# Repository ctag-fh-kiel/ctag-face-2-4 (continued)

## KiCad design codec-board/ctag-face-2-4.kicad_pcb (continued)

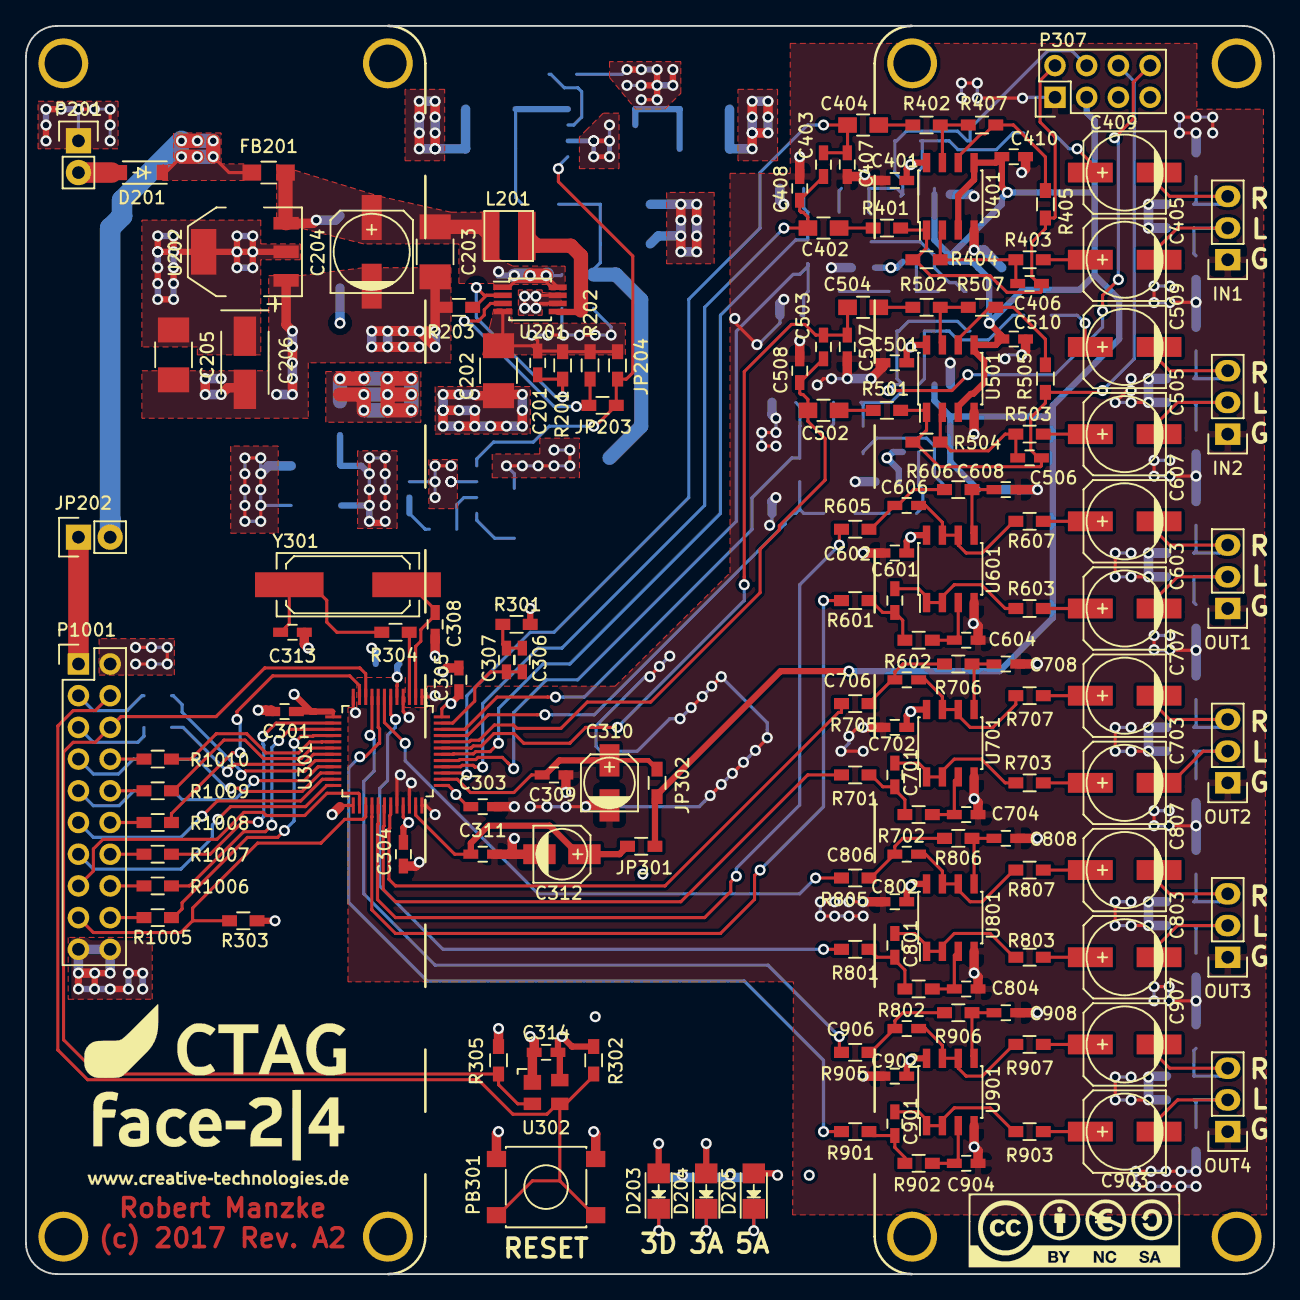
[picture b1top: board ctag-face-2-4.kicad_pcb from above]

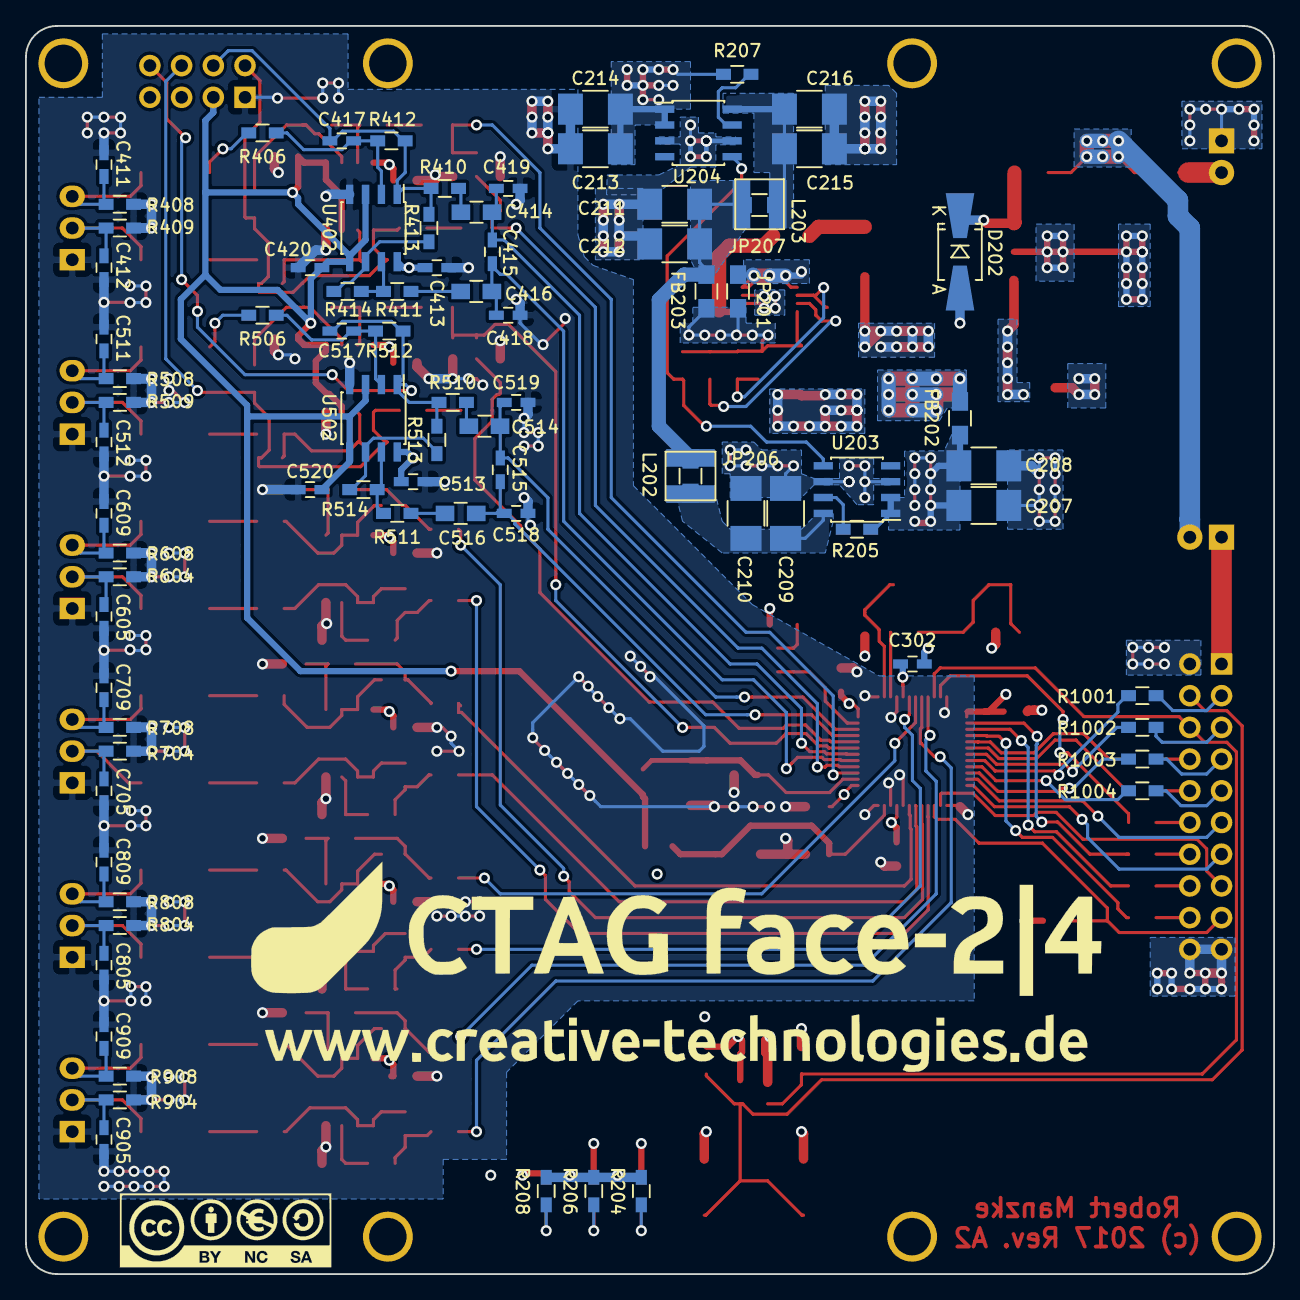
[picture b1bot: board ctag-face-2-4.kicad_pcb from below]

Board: 4 copper layers, 100.0 x 100.0 mm, 241 parts (84 on the bottom side), 143 nets.

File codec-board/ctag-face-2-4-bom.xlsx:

Mouser | Id | Designator | Package | Quantity | Designation | MfrNum | Remarks
x | 1 | C509,C204,C405,C409,C505,C603,C607,C703,C707,C803,C807,C903,C907 | c_elec_6.3x5.7 | 13 | 47uF | EEE-FC1C470P | Panasonic FC Type
x | 2 | C201 | C_0603_HandSoldering | 1 | 33pF | VJ0603A330JXACW1BC
x | 3 | C202 | C_1210_HandSoldering | 1 | 22uF | C3225X7R1C226K250AC | 10% X7R Highest Voltage Type possible
x | 4 | C203,C205,C207,C208,C209,C210,C211,C212,C213,C214,C215,C216 | C_1210_HandSoldering | 12 | 10uF | GRM32DR71E106KA12L | 10% X7R Highest Voltage Type possible
x | 5 | C206 | TantalC_SizeA_EIA-3216_HandSoldering | 1 | 100uF | TCNK107M006R0200
x | 6 | C301,C302,C303,C304,C305,C309,C311,C314,C401,C410,C413,C420,C501,C510,C513,C520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 | C_0603_HandSoldering | 20 | 100nF | C0603C104K5RACTU
x | 7 | C306 | C_0603_HandSoldering | 1 | 390pF | GRM1885C1H391JA01D
x | 8 | C307 | C_0603_HandSoldering | 1 | 5,6nF | C0603C562J5GACTU
x | 9 | C308,C313 | C_0603_HandSoldering | 2 | 22pF | C0603C220J5GACTU
x | 10 | C310,C312 | c_elec_4x5.7 | 2 | 10uF | EEE-FC1C100R
x | 11 | C402,C404,C414,C416,C502,C504,C514,C516 | C_0805_HandSoldering | 8 | 10uF | GRM21BR71A106KA73L
x | 12 | C403,C411,C412,C415,C503,C511,C512,C515 | C_0603_HandSoldering | 8 | 100pF | C0603C101J5GACTU
x | 13 | C406,C417,C506,C517,C601,C606,C701,C706,C801,C806,C901,C906 | C_0603_HandSoldering | 12 | 270pF | GRM1885C1H271JA01D
x | 14 | C407,C408,C418,C419,C507,C508,C518,C519 | C_0603_HandSoldering | 8 | 1nF | GCM188R71H102KA37D
x | 15 | C604,C608,C704,C708,C804,C808,C904,C908 | C_0603_HandSoldering | 8 | 200pF | GRM1885C2A201JA01D
x | 16 | C605,C609,C705,C709,C805,C809,C905,C909 | C_0603_HandSoldering | 8 | 3,3nF | C0603C332K5RACTU
x | 17 | D201 | SOD-123 | 1 | D_Schottky | STPS140Z
x | 18 | D203 | LED-1206 | 1 | LED3V3D | SML-LX1206GC-TR1
x | 19 | D204 | LED-1206 | 1 | LED3V3A | SML-LX1206GC-TR1
x | 20 | D205 | LED-1206 | 1 | LED5VA | SML-LX1206GC-TR1
x | 21 | JP201,JP206,JP207 | R_0805_HandSoldering | 3 | Jumper_NO_Small | RC0805JR-070RL
x | 22 | JP203,JP204,JP301,JP302 | R_0603_HandSoldering | 4 | Jumper_NO_Small | ERJ-3GEY0R00V
x | 23 | R201 | R_0603_HandSoldering | 1 | 115k | ERJ-3EKF1153V | Resistors all probably 1%, except digital section
x | 24 | R202,R303 | R_0603_HandSoldering | 2 | 1M | ERJ-3EKF1004V
x | 25 | R203 | R_0603_HandSoldering | 1 | 32k4 | ERJ-3EKF3242V
x | 26 | R204,R206 | R_0603_HandSoldering | 2 | 270 | ERJ-3EKF2700V
x | 27 | R205,R207,R302,R305,R408,R409,R508,R509,R604,R608,R704,R708,R804,R808,R904,R908 | R_0603_HandSoldering | 16 | 100k | ERJ-3EKF1003V
x | 28 | R208 | R_0603_HandSoldering | 1 | 620 | ERJ-3EKF6200V
x | 29 | R301 | R_0603_HandSoldering | 1 | 562 | ERJ-3EKF5620V
x | 30 | R304 | R_0603_HandSoldering | 1 | 100 | ERJ-3EKF1000V
x | 31 | R401,R402,R410,R411,R501,R502,R510,R511 | R_0603_HandSoldering | 8 | 237 | ERJ-3EKF2370V
x | 32 | R403,R404,R405,R406,R407,R412,R413,R414,R503,R504,R505,R506,R507,R512,R513,R514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 | R_0603_HandSoldering | 32 | 5k36 | ERJ-3EKF5361V
x | 33 | R603,R607,R703,R707,R803,R807,R903,R907 | R_0603_HandSoldering | 8 | 301 | ERJ-3EKF3010V
x | 34 | R1001,R1002,R1003,R1004,R1005,R1006,R1007,R1008,R1009,R1010 | R_0603_HandSoldering | 10 | 51 | ERJ-3EKF51R0V
x | 35 | SW301 | SW_SPST_PTS645 | 1 | SW_PUSH | PTS645SM43SMTR 92 LFS
x | 36 | U201 | MSOP-8_3x3mm_Pitch0.65mm | 1 | MCP1642B-ADJI/MS | MCP1642B-ADJI/MS
x | 37 | U202 | SOT-223 | 1 | TLV1117 | TLV1117-33IDCYR
x | 38 | U203 | SOIC-8_3.9x4.9mm_Pitch1.27mm | 1 | ADP7102ARDZ-3.3-R7 | ADP7102ARDZ-3.3-R7
x | 39 | U203,U204 | SOIC-8_3.9x4.9mm_Pitch1.27mm | 1 | ADP7102ARDZ-5.0-R7 | ADP7102ARDZ-5.0-R7
x | 40 | U301 | LQFP-48_7x7mm_Pitch0.5mm | 1 | AD1938 | AD1938YSTZ
x | 41 | U302 | SOT-143 | 1 | ADM811TARTZ | ADM811TARTZ-REEL7
x | 42 | U401,U402,U501,U502,U601,U701,U801,U901 | SOIC-8_3.9x4.9mm_Pitch1.27mm | 8 | 2CH-OPAMP | LME49721MAX/NOPB
x | 43 | Y301 | Q_49U3HMS | 1 | 24,576MHz | AT-24.576MAGK-T | Alternative
x | 44 | Y301 | Q_49U3HMS | 1 | 12,288MHz | AT-12.288MAGE-T
x | 45 | D202 | Diode-Universal-SMA-SMB_Handsoldering | 1 | FM4002 | FM4002
x | 46 | FB201,FB203 | R_0805_HandSoldering | 2 | 330R | 742792037 | Würth Beads
x | 47 | FB202 | R_0805_HandSoldering | 1 | 600R | 742792040
x | 48 | L201,L202,L203 | LPS4018 | 3 | 4.7uH | LPS4018-472MRC
x | 49 | P307 | DIL Socket 4+4 | 1 | ~ | M20-7830446 | Reichelt
x | 50 |  | Stiftleiste 40 Pins RM2,54 | 1 |  | M20-9734045
x | 51 |  | DIL Socket 10+10 | 1 |  | M20-7831046
x | 52 | C207, C208, C213, C214 | Alternative Configuration | 4 | 1uF | GRM32RR71H105KA01L | Configuration according to data sheet of ADPxxx
x | 53 | R604, R608 etc. | Alternative Configuration | 8 | 49k9 | ERJ-3EKF4992V

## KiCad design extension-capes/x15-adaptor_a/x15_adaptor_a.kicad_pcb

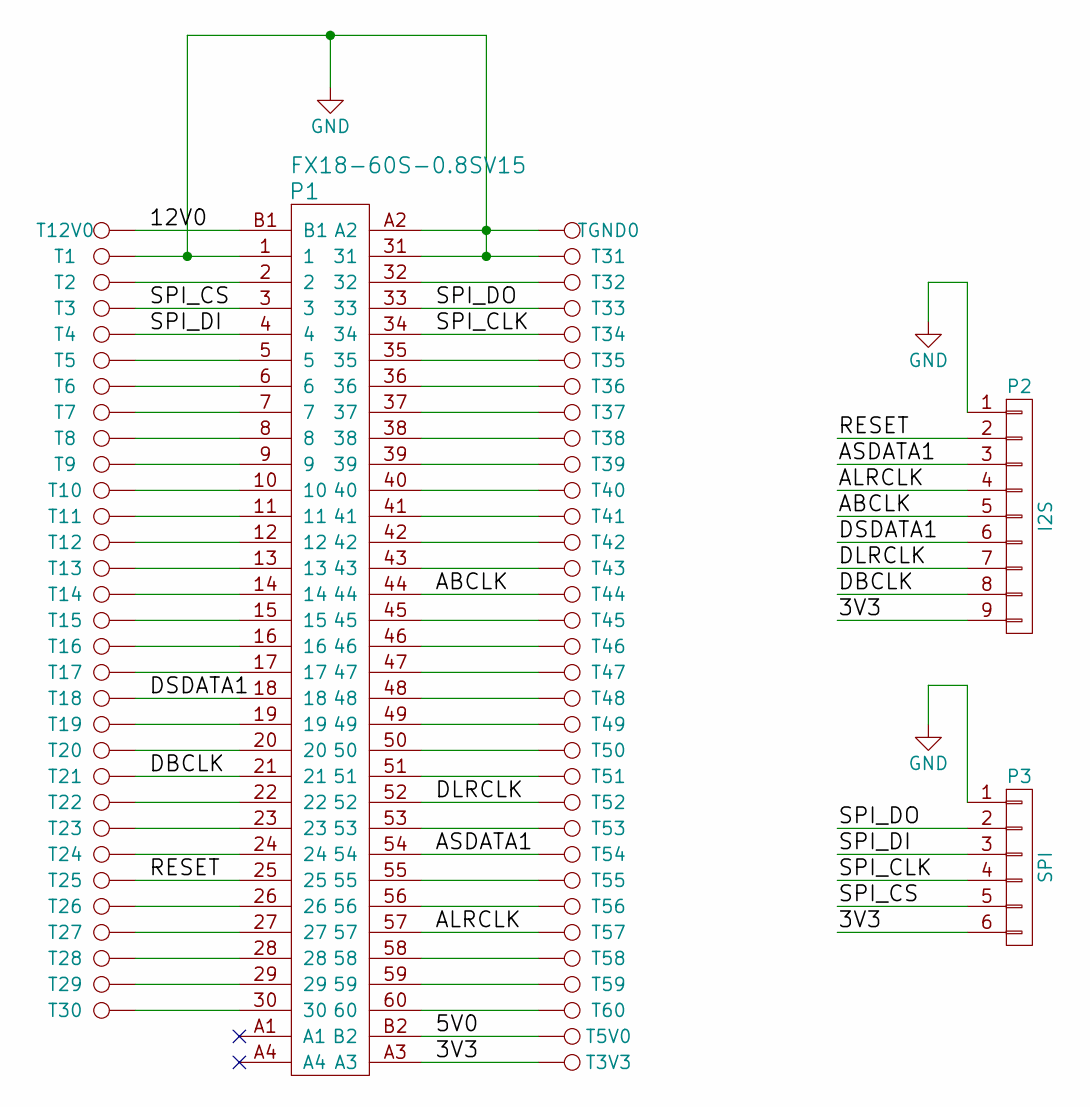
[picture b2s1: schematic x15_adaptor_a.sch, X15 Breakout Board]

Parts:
P1: FX18-60S-0.8SV15
P2: I2S; Pin_Header_Straight_1x09
P3: SPI; Pin_Header_Straight_1x06
T1, T2, T3, T3V3, T4, T5, T5V0, T6, T7, T8, T9, T10, T11, T12, T12V0, T13, T14, T15, T16, T17, T18, T19, T20, T21, T22, T23, T24, T25, T26, T27, T28, T29, T30, T31, T32, T33, T34, T35, T36, T37, T38, T39, T40, T41, T42, T43, T44, T45, T46, T47, T48, T49, T50, T51, T52, T53, T54, T55, T56, T57, T58, T59, T60: Testpin
TGND0: Testpin

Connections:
/3V3: P1.A3, P2.9, P3.6, T3V3.1
/5V0: P1.B2, T5V0.1
/12V0: P1.B1, T12V0.1
/ABCLK: P1.44, P2.5, T44.1
/ALRCLK: P1.57, P2.4, T57.1
/ASDATA1: P1.54, P2.3, T54.1
/DBCLK: P1.21, P2.8, T21.1
/DLRCLK: P1.52, P2.7, T52.1
/DSDATA1: P1.18, P2.6, T18.1
/RESET: P1.25, P2.2, T25.1
/SPI_CLK: P1.34, P3.4, T34.1
/SPI_CS: P1.3, P3.5, T3.1
/SPI_DI: P1.4, P3.3, T4.1
/SPI_DO: P1.33, P3.2, T33.1
GND: P1.1, P1.31, P1.A2, P2.1, P3.1, T1.1, T31.1, TGND0.1
unnamed: P1.2, T2.1
unnamed: P1.5, T5.1
unnamed: P1.6, T6.1
unnamed: P1.7, T7.1
unnamed: P1.8, T8.1
unnamed: P1.9, T9.1
unnamed: P1.10, T10.1
unnamed: P1.11, T11.1
unnamed: P1.12, T12.1
unnamed: P1.13, T13.1
unnamed: P1.14, T14.1
unnamed: P1.15, T15.1
unnamed: P1.16, T16.1
unnamed: P1.17, T17.1
unnamed: P1.19, T19.1
unnamed: P1.20, T20.1
unnamed: P1.22, T22.1
unnamed: P1.23, T23.1
unnamed: P1.24, T24.1
unnamed: P1.26, T26.1
unnamed: P1.27, T27.1
unnamed: P1.28, T28.1
unnamed: P1.29, T29.1
unnamed: P1.30, T30.1
unnamed: P1.32, T32.1
unnamed: P1.35, T35.1
unnamed: P1.36, T36.1
unnamed: P1.37, T37.1
unnamed: P1.38, T38.1
unnamed: P1.39, T39.1
unnamed: P1.40, T40.1
unnamed: P1.41, T41.1
unnamed: P1.42, T42.1
unnamed: P1.43, T43.1
unnamed: P1.45, T45.1
unnamed: P1.46, T46.1
unnamed: P1.47, T47.1
unnamed: P1.48, T48.1
unnamed: P1.49, T49.1
unnamed: P1.50, T50.1
unnamed: P1.51, T51.1
unnamed: P1.53, T53.1
unnamed: P1.55, T55.1
unnamed: P1.56, T56.1
unnamed: P1.58, T58.1
unnamed: P1.59, T59.1
unnamed: P1.60, T60.1

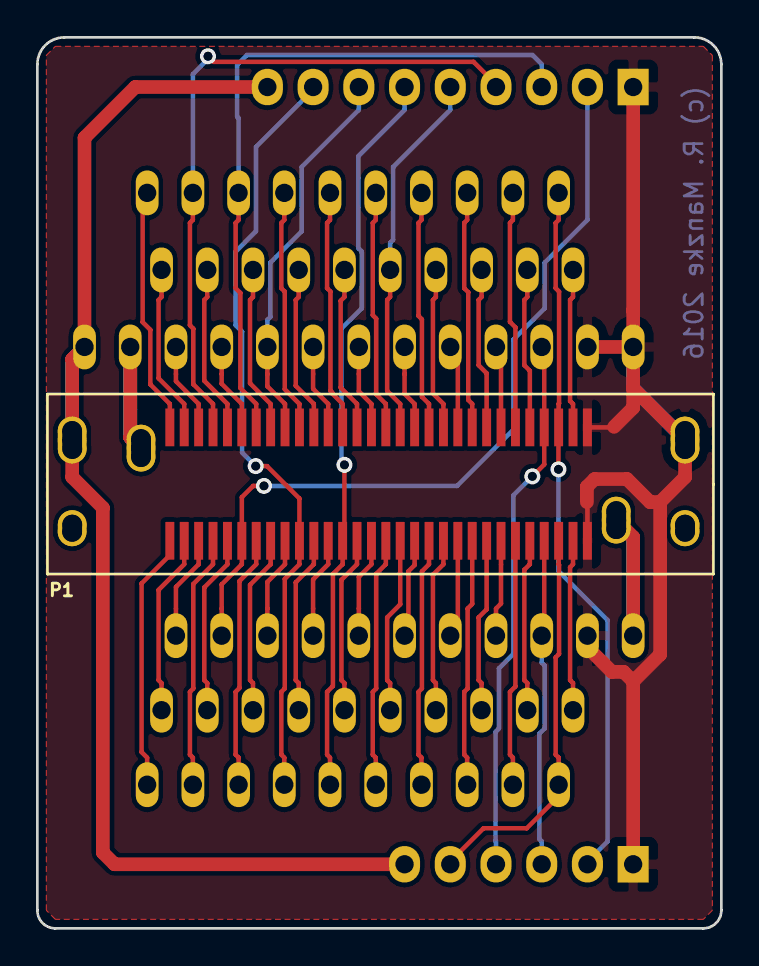
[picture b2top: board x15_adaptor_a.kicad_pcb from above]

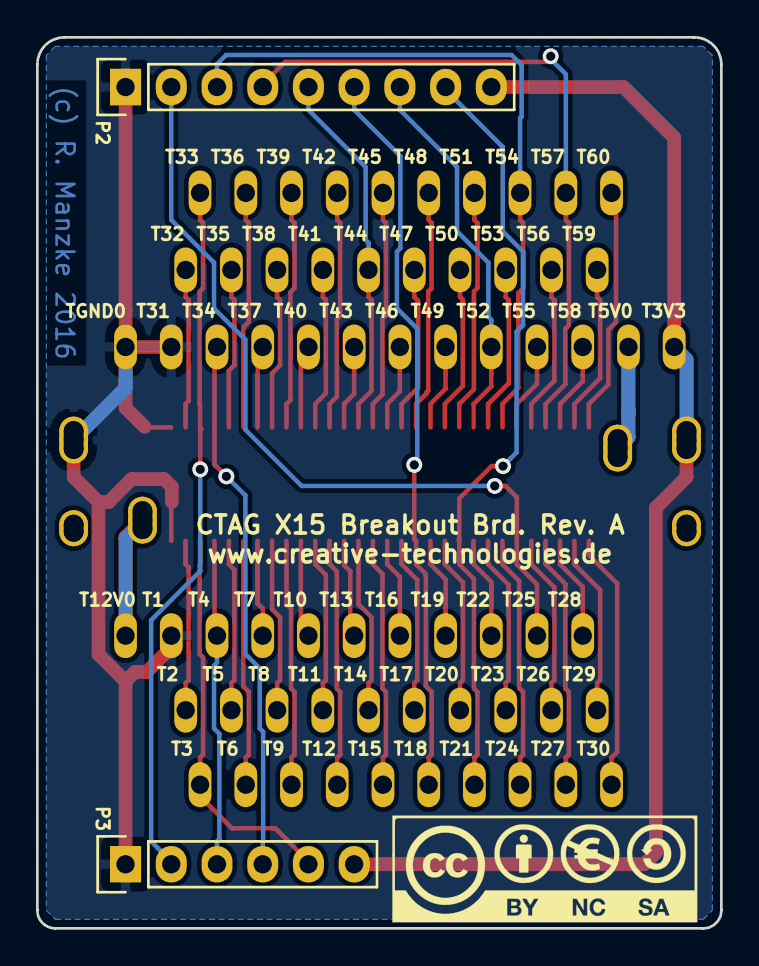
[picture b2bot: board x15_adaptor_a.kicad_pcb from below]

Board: 2 copper layers, 38.0 x 49.5 mm, 67 parts (66 on the bottom side), 62 nets.

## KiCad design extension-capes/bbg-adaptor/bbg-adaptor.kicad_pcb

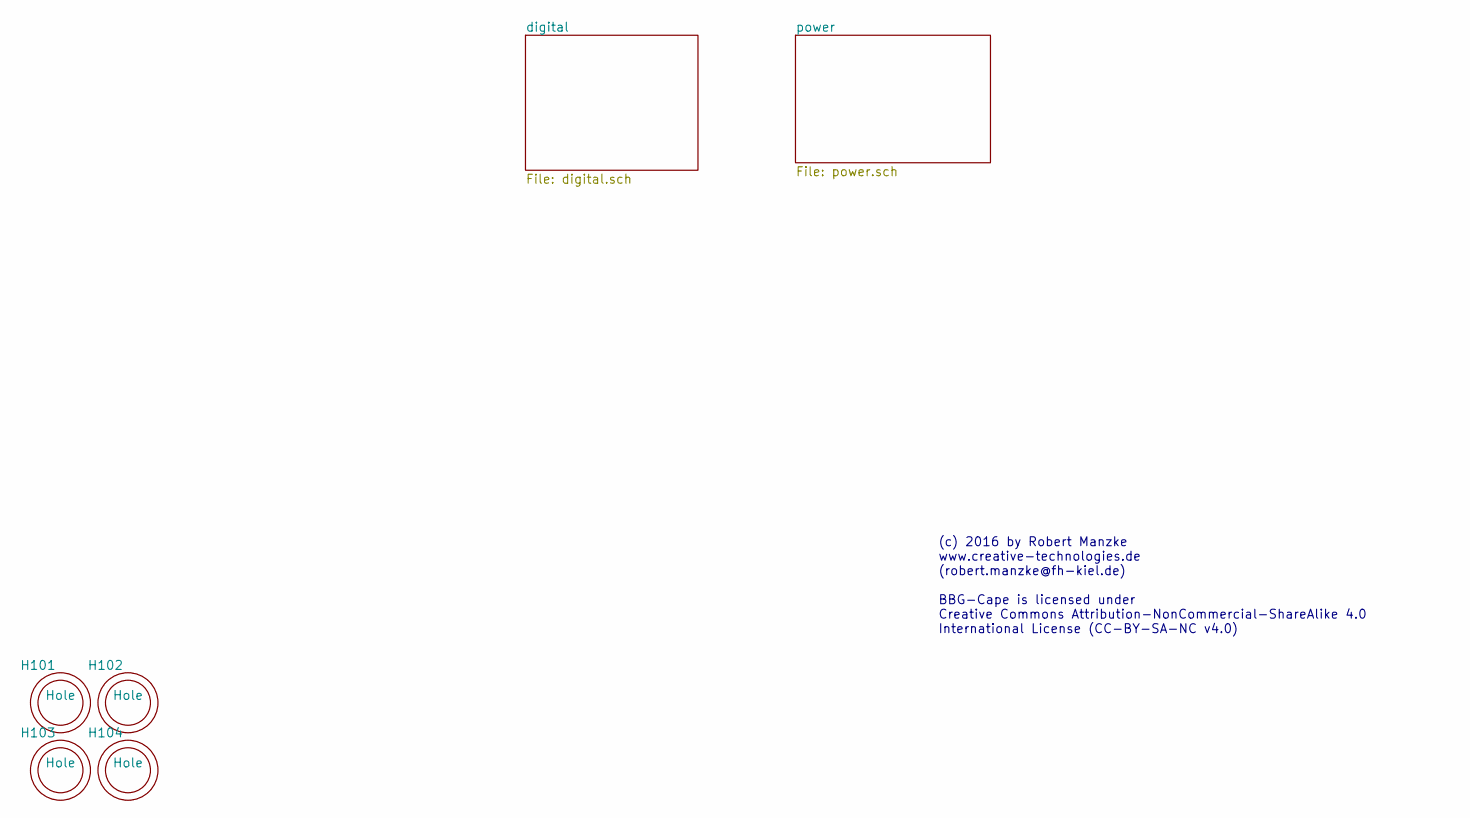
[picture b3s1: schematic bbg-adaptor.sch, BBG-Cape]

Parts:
H101, H102, H103, H104: Hole; Hole_3mm

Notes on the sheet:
(c) 2016 by Robert Manzke www.creative-technologies.de (robert.manzke@fh-kiel.de) BBG-Cape is licensed under Creative Commons Attribution-NonCommercial-ShareAlike 4.0 International License (CC-BY-SA-NC v4.0)

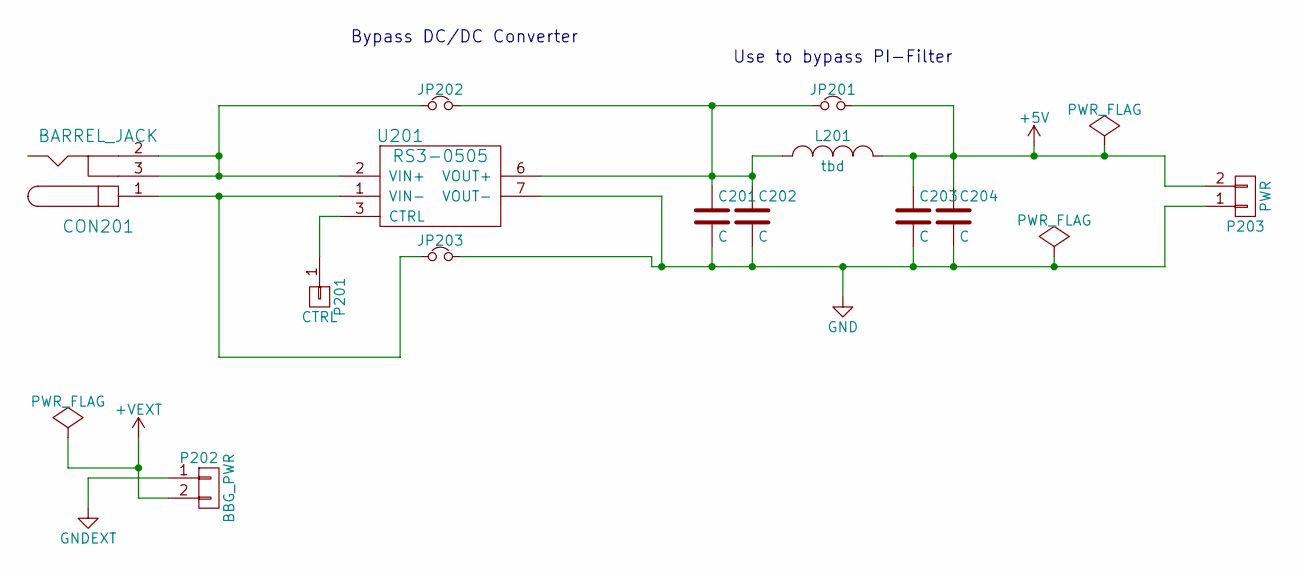
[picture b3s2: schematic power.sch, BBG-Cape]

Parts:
C201, C202, C203, C204: C; C_1210_HandSoldering
CON201: BARREL_JACK; BARELL_CLIFF_DC10L
JP201, JP202, JP203: Jumper_NC_Small; R_0805_HandSoldering
L201: tbd; LPS4018
P201: CTRL; Pin_Header_Straight_1x01
P202: BBG_PWR; Pin_Header_Straight_1x02
P203: PWR; Pin_Header_Straight_1x02
U201: RS3-0505

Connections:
+5V: C203.1, C204.1, JP201.2, L201.2, P203.2
+VEXT: P202.2; also elsewhere on the board
GND: C201.2, C202.2, C203.2, C204.2, JP203.2, P203.1, U201.7 (VOUT-); also elsewhere on the board
GNDEXT: P202.1; also elsewhere on the board
unnamed: C201.1, C202.1, JP201.1, JP202.2, L201.1, U201.6 (VOUT+)
unnamed: CON201.1, JP203.1, U201.1 (VIN-)
unnamed: CON201.2, CON201.3, JP202.1, U201.2 (VIN+)
unnamed: P201.1, U201.3 (CTRL)

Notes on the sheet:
Use to bypass PI-Filter
Bypass DC/DC Converter

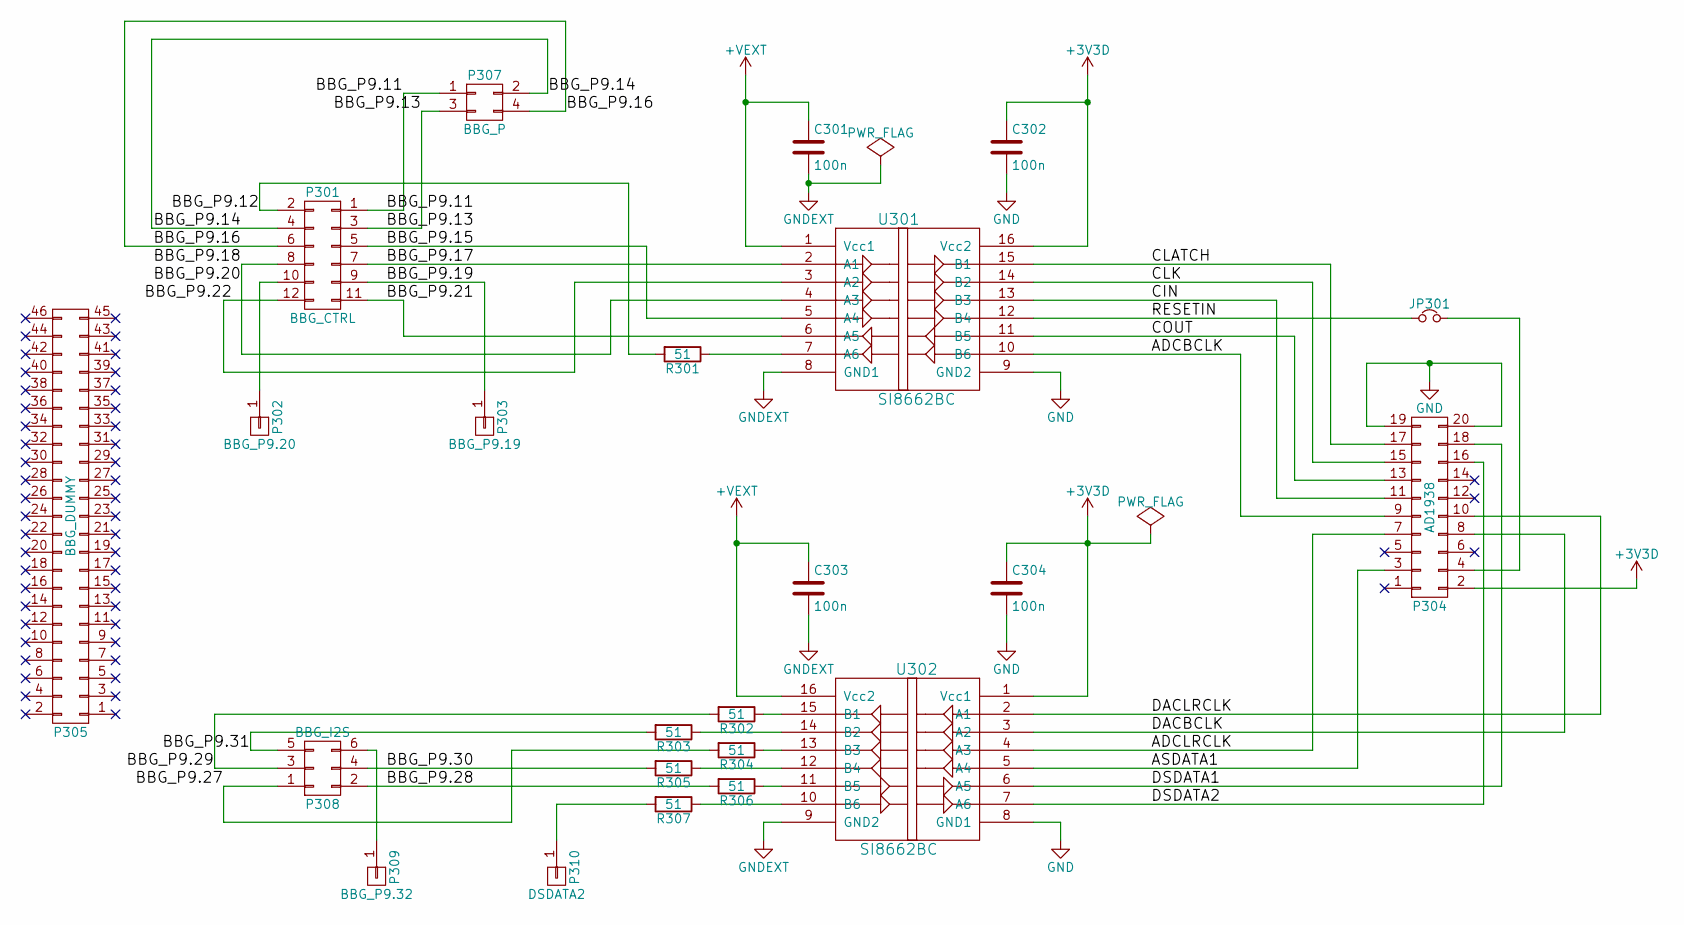
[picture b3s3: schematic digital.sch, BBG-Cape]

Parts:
C301, C302, C303, C304: 100n; C_0603_HandSoldering
JP301: Jumper_NC_Small; R_0603_HandSoldering
P301: BBG_CTRL; Pin_Header_Straight_2x06
P302: BBG_P9.20; Pin_Header_Straight_1x01
P303: BBG_P9.19; Pin_Header_Straight_1x01
P304: AD1938; Pin_Header_Straight_2x10
P305: BBG_DUMMY; Pin_Header_Straight_2x23
P307: BBG_P; Pin_Header_Straight_2x02
P308: BBG_I2S; Pin_Header_Straight_2x03
P309: BBG_P9.32; Pin_Header_Straight_1x01
P310: DSDATA2; Pin_Header_Straight_1x01
R301, R302, R303, R304, R305, R306, R307: 51; R_0603_HandSoldering
U301, U302: SI8662BC; SOIC-16_3.9x9.9mm_Pitch1.27mm

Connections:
+3V3D: C302.1, C304.1, P304.2, U301.16 (Vcc2), U302.1 (Vcc1)
+VEXT: C301.1, C303.1, U301.1 (Vcc1), U302.16 (Vcc2); also elsewhere on the board
/digital/ADCBCLK: P304.9, U301.10 (B6)
/digital/ADCLRCLK: P304.7, U302.4 (A3)
/digital/ASDATA1: P304.3, U302.5 (A4)
/digital/BBG_P9.11: P301.1, P307.1
/digital/BBG_P9.12: P301.2, R301.2
/digital/BBG_P9.13: P301.3, P307.3
/digital/BBG_P9.14: P301.4, P307.2
/digital/BBG_P9.15: P301.5, U301.5 (A4)
/digital/BBG_P9.16: P301.6, P307.4
/digital/BBG_P9.17: P301.7, U301.2 (A1)
/digital/BBG_P9.18: P301.8, U301.4 (A3)
/digital/BBG_P9.19: P301.9, P303.1
/digital/BBG_P9.21: P301.11, U301.6 (A5)
/digital/BBG_P9.22: P301.12, U301.3 (A2)
/digital/BBG_P9.27: P308.1, R304.2
/digital/BBG_P9.28: P308.2, R306.2
/digital/BBG_P9.29: P308.3, R302.2
/digital/BBG_P9.30: P308.4, R305.2
/digital/BBG_P9.31: P308.5, R303.2
/digital/CIN: P304.11, U301.13 (B3)
/digital/CLATCH: P304.17, U301.15 (B1)
/digital/CLK: P304.15, U301.14 (B2)
/digital/COUT: P304.13, U301.11 (B5)
/digital/DACBCLK: P304.8, U302.3 (A2)
/digital/DACLRCLK: P304.10, U302.2 (A1)
/digital/DSDATA1: P304.18, U302.6 (A5)
/digital/DSDATA2: P304.16, U302.7 (A6)
/digital/RESETIN: JP301.1, U301.12 (B4)
GND: C302.2, C304.2, P304.19, P304.20, U301.9 (GND2), U302.8 (GND1); also elsewhere on the board
GNDEXT: C301.2, C303.2, U301.8 (GND1), U302.9 (GND2); also elsewhere on the board
unnamed: JP301.2, P304.4
unnamed: P301.10, P302.1
unnamed: P308.6, P309.1
unnamed: P310.1, R307.2
unnamed: R301.1, U301.7 (A6)
unnamed: R302.1, U302.15 (B1)
unnamed: R303.1, U302.14 (B2)
unnamed: R304.1, U302.13 (B3)
unnamed: R305.1, U302.12 (B4)
unnamed: R306.1, U302.11 (B5)
unnamed: R307.1, U302.10 (B6)

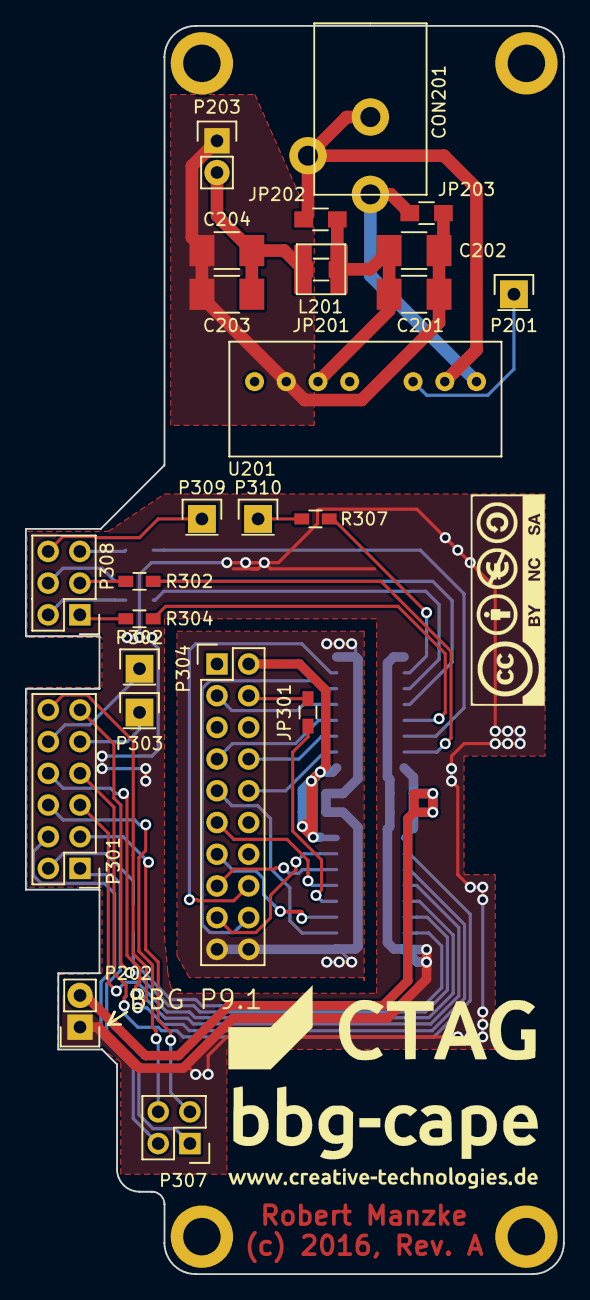
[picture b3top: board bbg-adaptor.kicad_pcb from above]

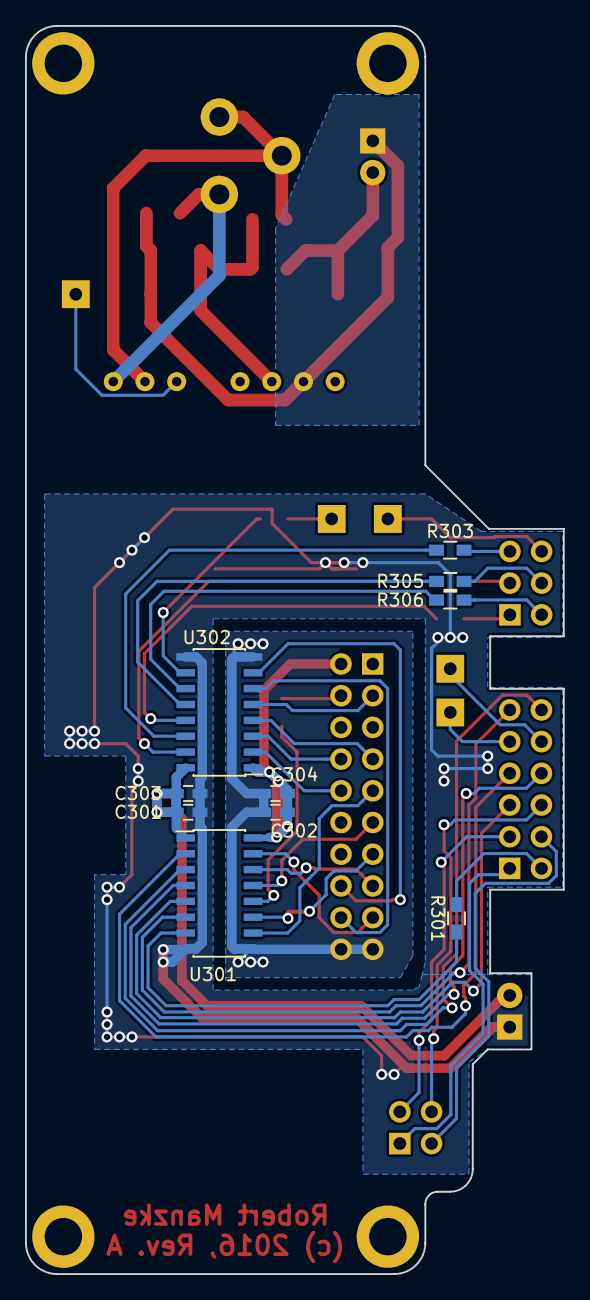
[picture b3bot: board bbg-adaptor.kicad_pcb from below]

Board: 2 copper layers, 43.1 x 100.0 mm, 39 parts (10 on the bottom side), 48 nets.

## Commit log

2015-11-03 Changed SW SPI pins due to collision with Bela
2015-11-03 added separate device tree overlays for 8 channel and 16 channel via software SPI
2015-11-03 added ALSA configurations for 8 and 16 audio channels
2015-11-03 Updated SW SPI pins
2015-11-03 bug fixes in device tree overlays for software SPI
2016-02-13 initial public
2016-02-14 Added kernel compilation guide and pin connections table.
2016-02-14 Rename Debian_Image.md to Quick_Start_Guide_Debian_Image.md
2016-02-14 Rename Evaluation_Script.md to Automatic_Evaluation_User_Guide.md
2016-02-27 Updated kernel compilation guide
2016-02-27 Added device tree overlays
2016-06-01 added X15 breakout boards for testing, review stage
2016-06-02 x15 adaptor production stage
2016-06-03 changed diameters of test pin holes
2016-06-03 changed readme.md to include X15 adaptor
2016-06-05 added multiple holes for oblong shape to account for boardhouse capabilities
2016-09-05 found bug and put it in readme.md, not fixed yet
2016-10-02 Added device tree overlay for SPI via GPIO (bitbanging)
2016-10-02 Updated device tree overlay for SW SPI
2016-10-12 Added SW SPI pin description
2016-12-12 updated device tree overlays for software SPI and daisy chained AD1938
2016-12-20 fixed bug in device tree overlays for software SPI and 16 channel daisy chain
2017-03-19 Added init.d scripts to load device tree overlays for CTAG face2|4 and CTAG Beast
2017-03-19 Fixed naming of initd script for CTAG Beast.
2017-04-12 Added pin connections for BeagleBoard-X15
2017-04-16 updated links!
2017-04-16 updated links
2017-04-16 typos
2017-04-18 added new pin connections for sw spi
2017-05-13 Added properties to configure bit delay of codec and McASP in device tree overlay.
2017-05-13 Removed spi-gpio from device tree overlay.
2017-06-04 changed page layout
2017-06-04 fixed polarity bug on IN2
2017-06-04 changed readme
2017-06-04 finalized Rev A2
2017-07-04 Changed default bit delay configuration for CTAG audio cards without isolators.
2017-07-31 Fixed bug which caused wrong channel order when using the Beast (16 channels).
2017-11-13 Update Pin_Connections.md
    Removed McASP receive pin connections of CTAG face2|4 Rev. B
2021-11-07 Update KiCad link
    See https://forum.kicad.info/t/warning-avoid-all-links-to-kicad-pcb-org-use-kicad-org/31521/
